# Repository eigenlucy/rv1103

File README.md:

# Rockchip RV1103

Implementation based on the Luckfox Mini dev board

Created by lucy moglia <eigenlucy@proton.me>

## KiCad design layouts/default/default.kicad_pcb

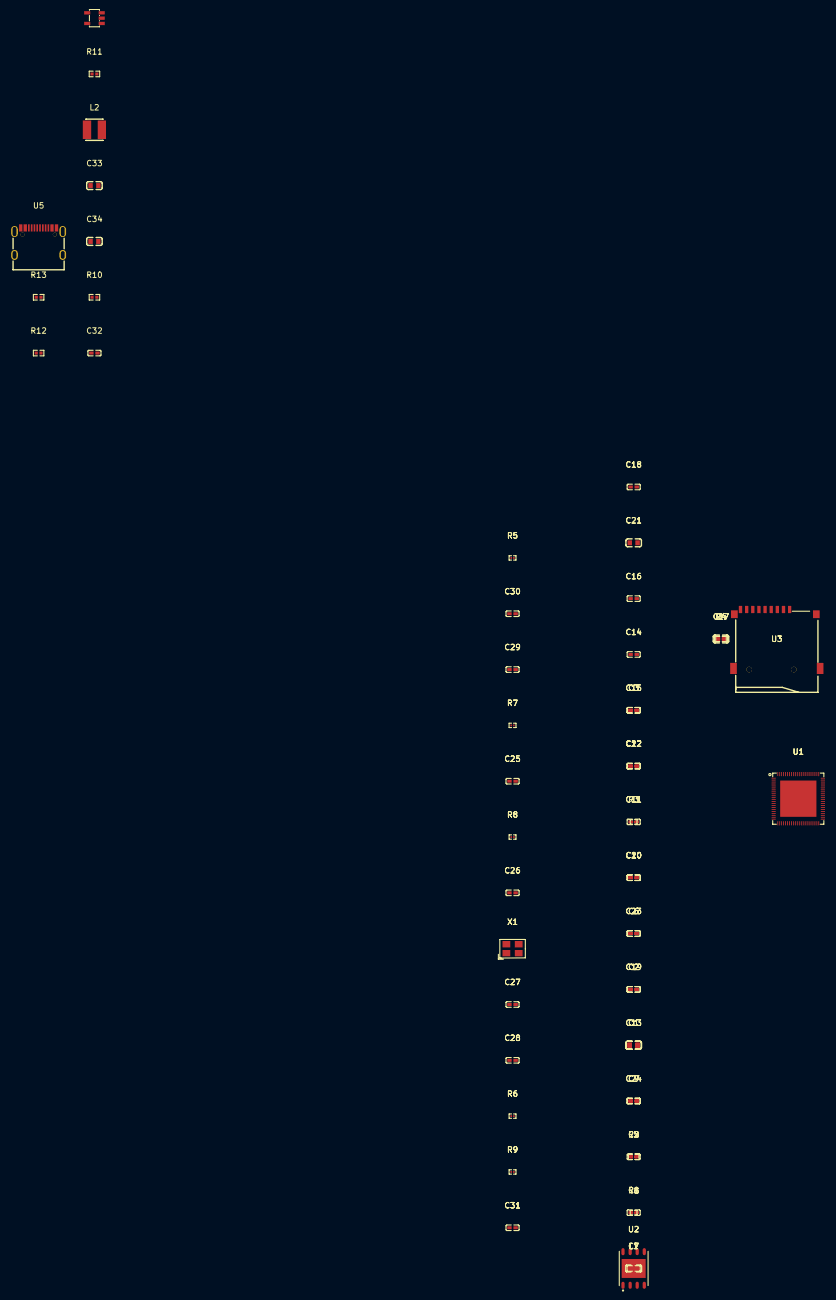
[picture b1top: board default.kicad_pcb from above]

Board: 2 copper layers, 55 parts (0 on the bottom side), 32 nets, no tracks yet.

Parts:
C1, C13, C17, C21, C33, C34: 100nF ±10% 50V X7R; C0603-bd72f6
C2, C3, C4, C5, C6, C7, C8, C9, C10, C11, C12, C14, C15, C16, C18, C19, C20, C22, C23, C24, C25, C26, C27, C28, C29, C30, C31, C32: 100nF ±10% 16V X7R; C0402-b3ef17
L1: L0603-9cac2b
L2: IND-SMD_L3.0-W3.0-a13401
R1, R3, R5, R6, R7, R8, R9: 0Ω 50mW; R0201-27027e
R2, R4: 1kΩ ±1% 62.5mW; R0402-56259e
R10: 200kΩ ±1% 62.5mW; R0402-56259e
R11: 100kΩ ±1% 62.5mW; R0402-56259e
R12, R13: 4.7kΩ ±1% 62.5mW; R0402-56259e
U1: QFN-88_L9.0-W9.0-P0.35-TL-EP6.5-4d2c2f
U2: WSON-8_L6.0-W5.0-P1.27-BL-EP-5c84f1
U3: TF-SMD_TF-01A
U4: SOT-23-5_L3.0-W1.7-P0.95-LS2.8-BR-9d80aa
U5: USB-C-SMD_KH-TYPE-C-16P
X1: CRYSTAL-SMD_4P-L3.2-W2.5-BL-2-acd8b5

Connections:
A5: R12.1, U5.A5
A7: U5.A7, U5.B7
CC2: R13.1, U5.B5
DP2: U5.A6, U5.B6
DRAM_ZQ: R1.1, U1.37
ETH_EXTR: R4.1, U1.72
FB: C32.2, R10.1, R11.2, U4.5
FSPI_CLK: U1.33, U2.7
FSPI_CS0N: U1.32, U2.1
FSPI_D0_GPIO4_A4_u: U1.29, U2.5
FSPI_D1_GPIO4_A3_u: U1.30, U2.2
FSPI_D2_GPIO4_A2_u: R7.2, U1.31, U2.3
FSPI_D3_GPIO4_A6_u: R8.2, U1.28, U2.6
GPIO3_VCC: C29.1, U1.27
MIPI_LVDS_D2P: U1.77, U1.81
MIPI_LVDS_MCLK0_FL: R9.2, U1.1
OSC1: C26.1, X1.1
OSC2: C25.1, R5.2, X1.3
OSC_XIN: R6.2, U1.45
OSC_XOUT: R5.1, R6.1, U1.46
SDMMC_CLK_FL: R3.2, U1.11
SW: L2.1, U4.3
VBUS: U5.A4, U5.A9, U5.B4, U5.B9
VCC_DDR: U1.34, U1.35, U1.40
gnd: C1.2, C2.2, C3.2, C4.2, C5.2, C6.2, C7.2, C8.2, C9.2, C10.2, C11.2, C12.2, C13.2, C14.2, C15.2, C21.2, C22.2, C23.2, C24.2, C25.2, C26.2, C27.2, C28.2, C29.2, C30.2, C31.2, C33.2, C34.2, R1.2, R4.2, R10.2, U1.89, U2.4, U2.9, U4.2, X1.2, X1.4
hv: C21.1, C22.1, L1.2
hv-2: C1.1, C2.1, C3.1, C4.1, C5.1, C6.1, C7.1, C8.1, C9.1, C10.1, C11.1, C12.1, C33.1, U1.6, U1.36, U1.39, U1.44, U1.58, U1.73, U1.74, U1.75, U4.4
hv-3: C32.1, C34.1, L2.2, R11.1
hv-5: C14.1, C15.1, C27.1, C28.1, C30.1, C31.1, R7.1, R8.1, U1.7, U1.20, U1.59, U1.71, U2.8
hv-6: C23.1, C24.1, L1.1, R2.1, U1.38
sd-gnd: U3.6, U3.10, U3.11, U3.12, U3.13
usbc-gnd: R12.2, R13.2, U5.1, U5.2, U5.3, U5.4, U5.A1, U5.A12, U5.B1, U5.B12

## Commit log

2025-04-28 laptop push
2025-04-28 initial build, migrating to V6
2025-04-28 added flash and sd card
2025-04-28 more work
2025-04-28 fixed errors
2025-04-29 edits
